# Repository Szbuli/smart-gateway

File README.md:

# Smart gateway
## build
`'docker buildx create --driver=docker-container --name=multi --use`
### mqtt-gateway
`docker buildx build -t szbuli/mqtt-gateway:latest -t szbuli/mqtt-gateway:1.0.1 --platform linux/arm64,linux/arm64/v8 --push .`
### resource-monitor
`docker buildx build -t szbuli/resource-monitor:latest -t szbuli/resource-monitor:1.0.0 --platform linux/arm64,linux/arm64/v8 --push .`
## deploy

- start and upgrade
`sudo docker compose up --detach`
- logs
`sudo docker compose logs -f -t`
- restart a single service
`sudo docker compose restart zigbee2mqtt`

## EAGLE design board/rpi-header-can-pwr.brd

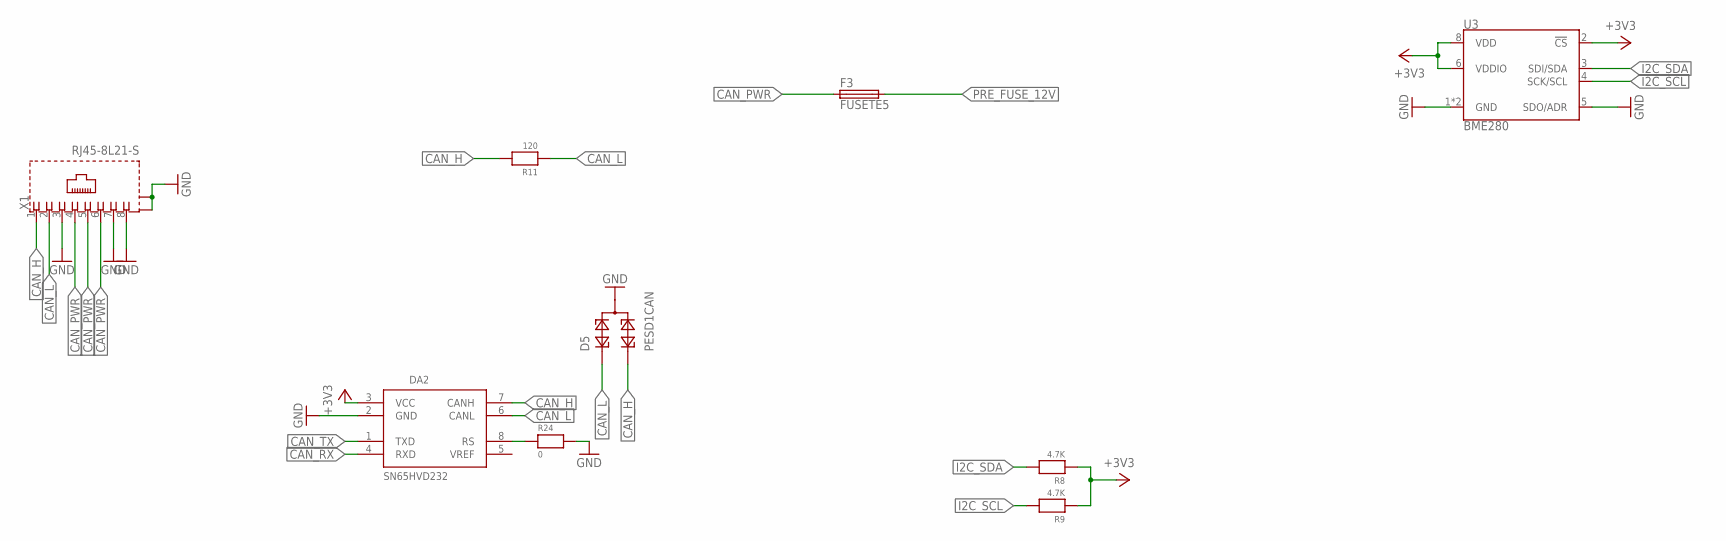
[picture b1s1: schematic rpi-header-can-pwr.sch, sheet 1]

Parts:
D5: PESD1CAN; SOT23
DA2: SN65HVD232; SO08
F3: FUSETE5; TE5
R8, R9: 4.7K; 0603
R11: 120; 0603
R24: 0; 0603
U3: BME280; LGA-8-2.5X2.5
X1: RJ45-8L21-S; RJ45-SHIELD1

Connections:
+3V3: DA2.3 (VCC), R8.1, R9.1, U3.2 (!CS), U3.6 (VDDIO), U3.8 (VDD); also elsewhere on the board
CAN_H: D5.2, DA2.7 (CANH), R11.2, X1.1
CAN_L: D5.1, DA2.6 (CANL), R11.1, X1.2
CAN_PWR: F3.1, X1.4, X1.5, X1.6
CAN_RX: DA2.4 (RXD); also elsewhere on the board
CAN_TX: DA2.1 (TXD); also elsewhere on the board
GND: D5.3, DA2.2 (GND), R24.2, U3.1 (GND), U3.5 (SDO/ADR), U3.7 (GND), X1.3, X1.7, X1.8, X1.S1 (S), X1.S2 (S); also elsewhere on the board
I2C_SCL: R9.2, U3.4 (SCK/SCL); also elsewhere on the board
I2C_SDA: R8.2, U3.3 (SDI/SDA); also elsewhere on the board
unnamed: DA2.8 (RS), R24.1
PRE_FUSE_12V: F3.2; also elsewhere on the board

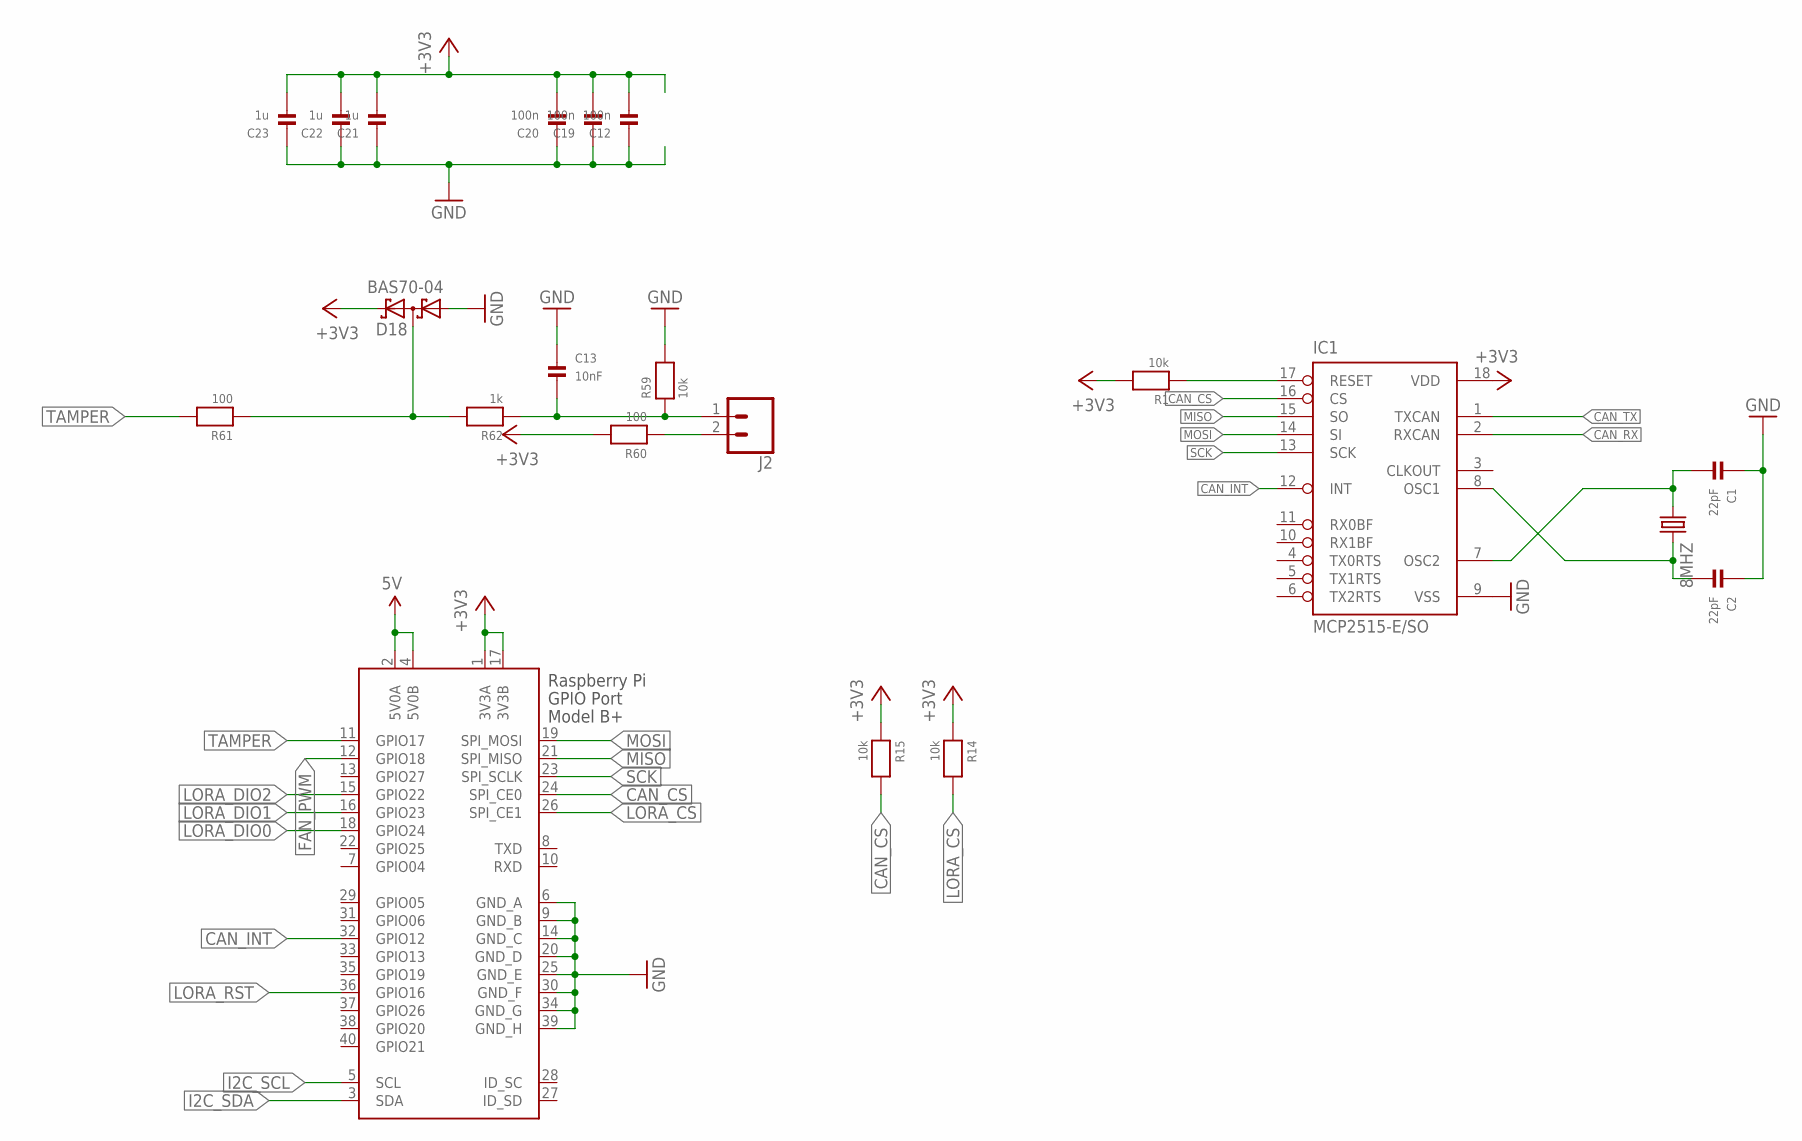
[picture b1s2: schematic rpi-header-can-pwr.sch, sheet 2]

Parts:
8MHZ: CRYSTALHC49UP; HC49UP
C1, C2: 22pF; 0603
C12, C19, C20: 100n; 0603
C13: 10nF; 0603
C21, C22, C23: 1u; 0603
D18: BAS70-04; SOT23
IC1: MCP2515-E/SO; SO18L
J2: CONN_023.5MM; SCREWTERMINAL-3.5MM-2
R1, R14, R15, R59: 10k; 0603
R60, R61: 100; 0603
R62: 1k; 0603
X2: RASPI_BOARD_B+#_E3; RASPI_BOARD_B+_EDGES_3DRILL

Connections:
5V: X2.2 (5V0A), X2.4 (5V0B); also elsewhere on the board
+3V3: C12.2, C19.2, C20.2, C21.2, C22.2, C23.2, D18.2 (C2), IC1.18 (VDD), R1.2, R14.1, R15.1, R60.2, X2.1 (3V3A), X2.17 (3V3B); also elsewhere on the board
ASDASD: D18.3 (C1A2), R61.1, R62.2
CAN_CS: IC1.16 (CS), R15.2, X2.24 (SPI_CE0)
CAN_INT: IC1.12 (INT), X2.32 (GPIO12)
CAN_RX: IC1.2 (RXCAN); also elsewhere on the board
CAN_TX: IC1.1 (TXCAN); also elsewhere on the board
FAN_PWM: X2.12 (GPIO18); also elsewhere on the board
GND: C1.1, C2.1, C12.1, C13.1, C19.1, C20.1, C21.1, C22.1, C23.1, D18.1 (A1), IC1.9 (VSS), R59.2, X2.6 (GND_A), X2.9 (GND_B), X2.14 (GND_C), X2.20 (GND_D), X2.25 (GND_E), X2.30 (GND_F), X2.34 (GND_G), X2.39 (GND_H); also elsewhere on the board
I2C_SCL: X2.5 (SCL); also elsewhere on the board
I2C_SDA: X2.3 (SDA); also elsewhere on the board
LORA_CS: R14.2, X2.26 (SPI_CE1); also elsewhere on the board
LORA_DIO0: X2.18 (GPIO24); also elsewhere on the board
LORA_DIO1: X2.16 (GPIO23); also elsewhere on the board
LORA_DIO2: X2.15 (GPIO22); also elsewhere on the board
LORA_RST: X2.36 (GPIO16); also elsewhere on the board
MISO: IC1.15 (SO), X2.21 (SPI_MISO); also elsewhere on the board
MOSI: IC1.14 (SI), X2.19 (SPI_MOSI); also elsewhere on the board
unnamed: 8MHZ.2, C2.2, IC1.8 (OSC1)
unnamed: 8MHZ.1, C1.2, IC1.7 (OSC2)
unnamed: J2.2, R60.1
unnamed: C13.2, J2.1, R59.1, R62.1
RS: IC1.17 (RESET), R1.1
SCK: IC1.13 (SCK), X2.23 (SPI_SCLK); also elsewhere on the board
TAMPER: R61.2, X2.11 (GPIO17)

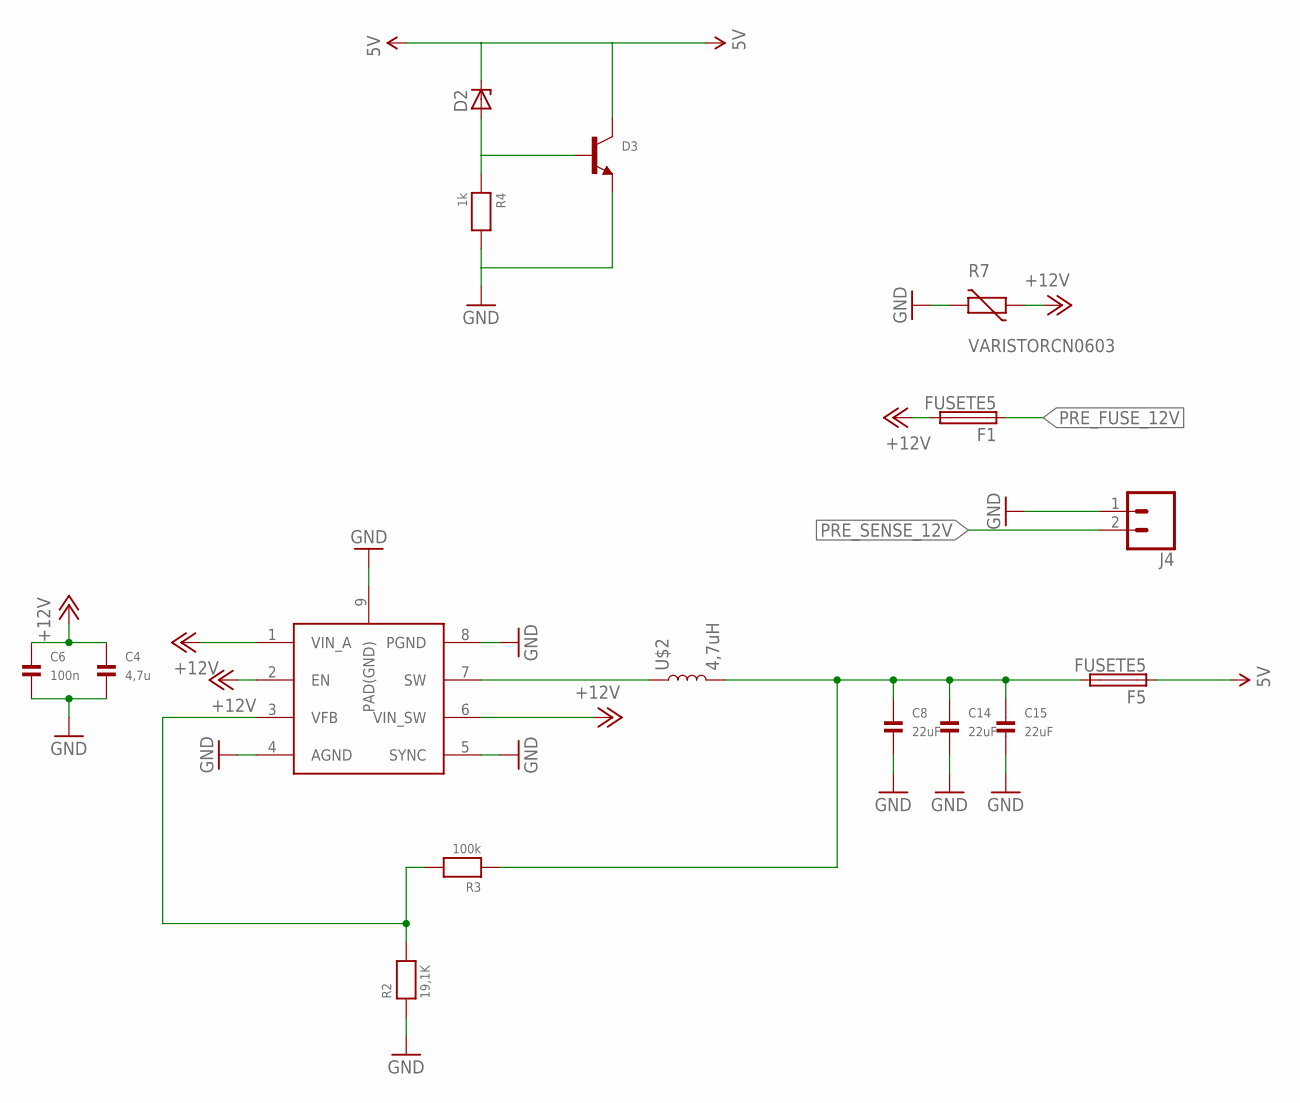
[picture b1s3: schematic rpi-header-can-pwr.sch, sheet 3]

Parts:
C4: 4,7u; 0805
C6: 100n; 0805
C8, C14, C15: 22uF; 0805
D2: ZENER-DIODESOD80C; SOD80C
D3: TRANSISTOR_NPNWIDE; SOT23-WIDE
F1, F5: FUSETE5; TE5
J4: CONN_025MM; SCREWTERMINAL-5MM-2
R2: 19,1K; 0603
R3: 100k; 0603
R4: 1k; 0603
R7: VARISTORCN0603; CT/CN0603
U$1: ST1S10; POWERSO-8
U$2: 4,7uH; 0504

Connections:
5V: D2.C, D3.3 (C), F5.1; also elsewhere on the board
+12V: C4.1, C6.1, F1.2, R7.1, U$1.1 (VIN_A), U$1.2 (EN), U$1.6 (VIN_SW)
GND: C4.2, C6.2, C8.2, C14.2, C15.2, D3.2 (E), J4.1, R2.1, R4.2, R7.2, U$1.4 (AGND), U$1.5 (SYNC), U$1.8 (PGND), U$1.9 (PAD(GND)); also elsewhere on the board
unnamed: R2.2, R3.2, U$1.3 (VFB)
unnamed: D2.A, D3.1 (B), R4.1
unnamed: U$1.7 (SW), U$2.1
unnamed: C8.1, C14.1, C15.1, F5.2, R3.1, U$2.2
PRE_FUSE_12V: F1.1; also elsewhere on the board
PRE_SENSE_12V: J4.2; also elsewhere on the board

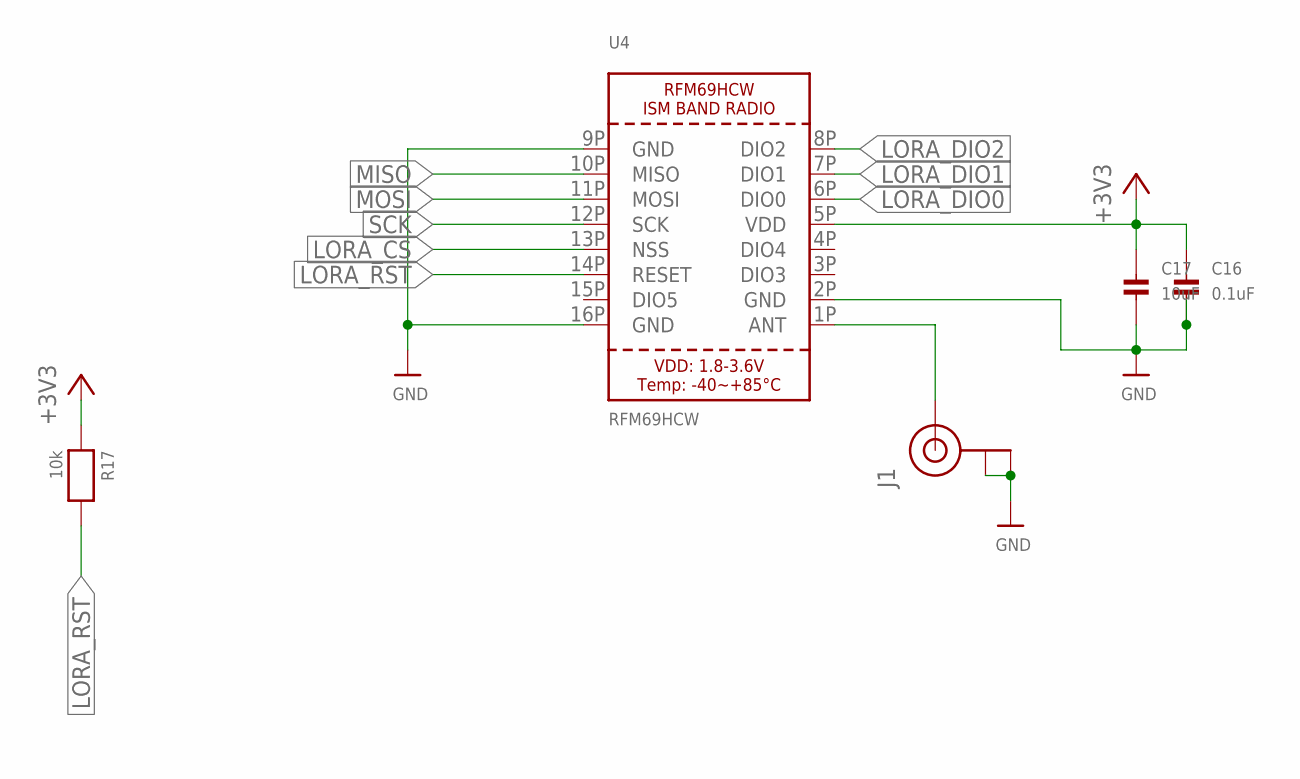
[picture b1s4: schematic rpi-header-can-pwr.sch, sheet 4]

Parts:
C16: 0.1uF; 0603
C17: 10uF; 0603
J1: U.FL
R17: 10k; 0603
U4: RFM69HCW; RFMHCW_SMT

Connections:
+3V3: C16.1, C17.1, R17.1, U4.5P (VDD); also elsewhere on the board
GND: C16.2, C17.2, J1.P$1 (GND), J1.P$2 (GND), U4.2P (GND), U4.9P (GND), U4.16P (GND); also elsewhere on the board
LORA_CS: U4.13P (NSS); also elsewhere on the board
LORA_DIO0: U4.6P (DIO0); also elsewhere on the board
LORA_DIO1: U4.7P (DIO1); also elsewhere on the board
LORA_DIO2: U4.8P (DIO2); also elsewhere on the board
LORA_RST: R17.2, U4.14P (RESET); also elsewhere on the board
MISO: U4.10P (MISO); also elsewhere on the board
MOSI: U4.11P (MOSI); also elsewhere on the board
unnamed: J1.P$3 (SIGNAL), U4.1P (ANT)
SCK: U4.12P (SCK); also elsewhere on the board

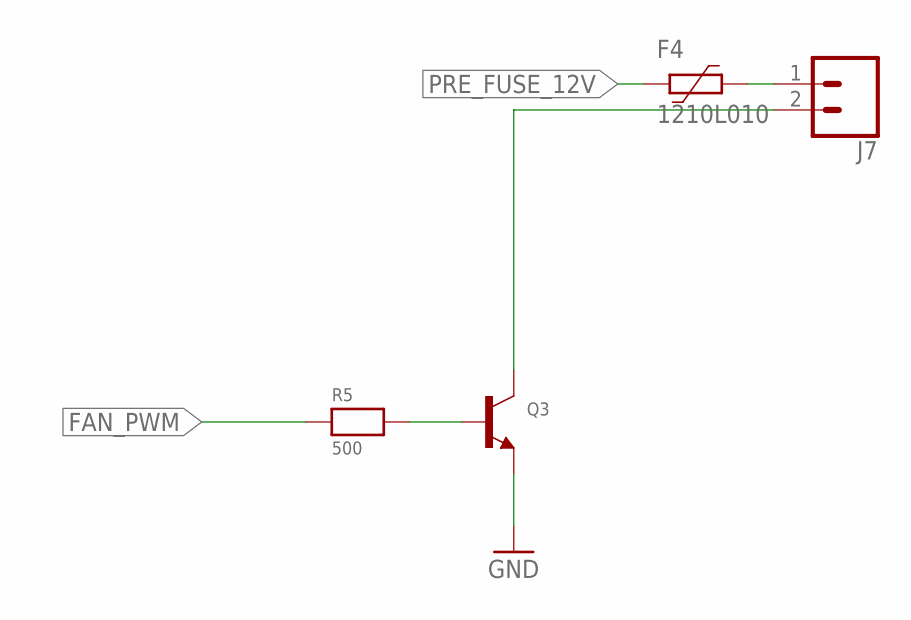
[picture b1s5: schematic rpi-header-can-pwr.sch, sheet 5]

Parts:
F4: 1210L010; 1210L
J7: CONN_023.5MM; SCREWTERMINAL-3.5MM-2
Q3: TRANSISTOR_NPNWIDE; SOT23-WIDE
R5: 500; 0603

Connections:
FAN_PWM: R5.1; also elsewhere on the board
GND: Q3.2 (E); also elsewhere on the board
unnamed: Q3.1 (B), R5.2
unnamed: F4.1, J7.1
unnamed: J7.2, Q3.3 (C)
PRE_FUSE_12V: F4.2; also elsewhere on the board

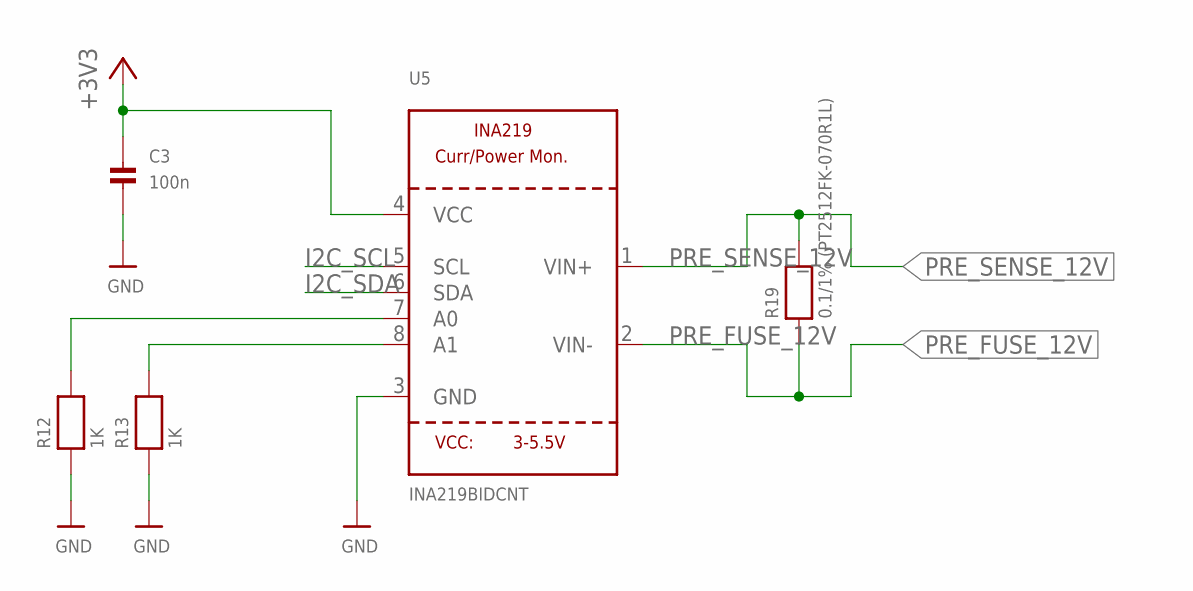
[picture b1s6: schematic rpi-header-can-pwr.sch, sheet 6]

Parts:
C3: 100n; 0603
R12, R13: 1K; 0603
R19: 0.1/1% (PT2512FK-070R1L); 2512
U5: INA219BIDCNT; SOT23-8

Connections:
+3V3: C3.1, U5.4 (VCC); also elsewhere on the board
GND: C3.2, R12.1, R13.1, U5.3 (GND); also elsewhere on the board
I2C_SCL: U5.5 (SCL); also elsewhere on the board
I2C_SDA: U5.6 (SDA); also elsewhere on the board
unnamed: R13.2, U5.8 (A1)
unnamed: R12.2, U5.7 (A0)
PRE_FUSE_12V: R19.1, U5.2 (VIN-); also elsewhere on the board
PRE_SENSE_12V: R19.2, U5.1 (VIN+); also elsewhere on the board

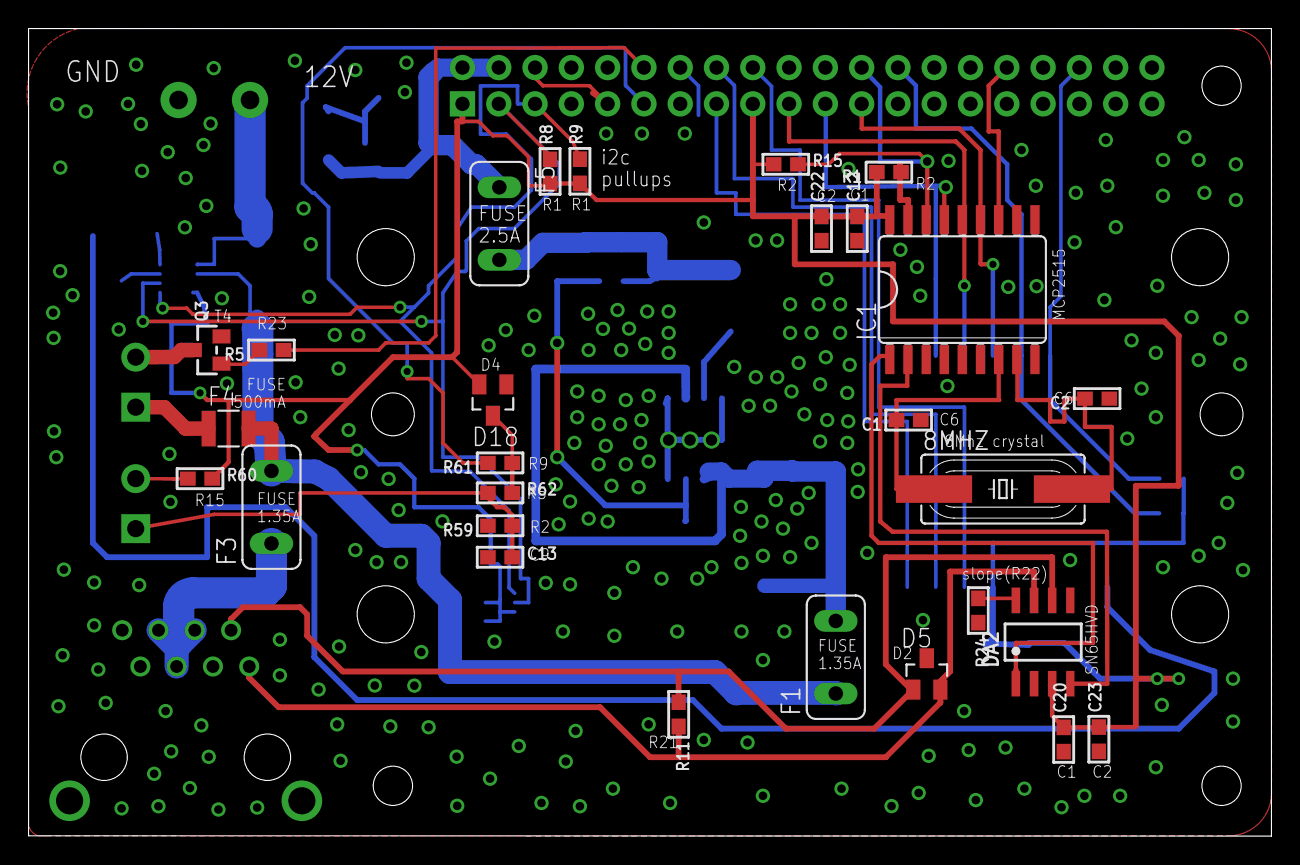
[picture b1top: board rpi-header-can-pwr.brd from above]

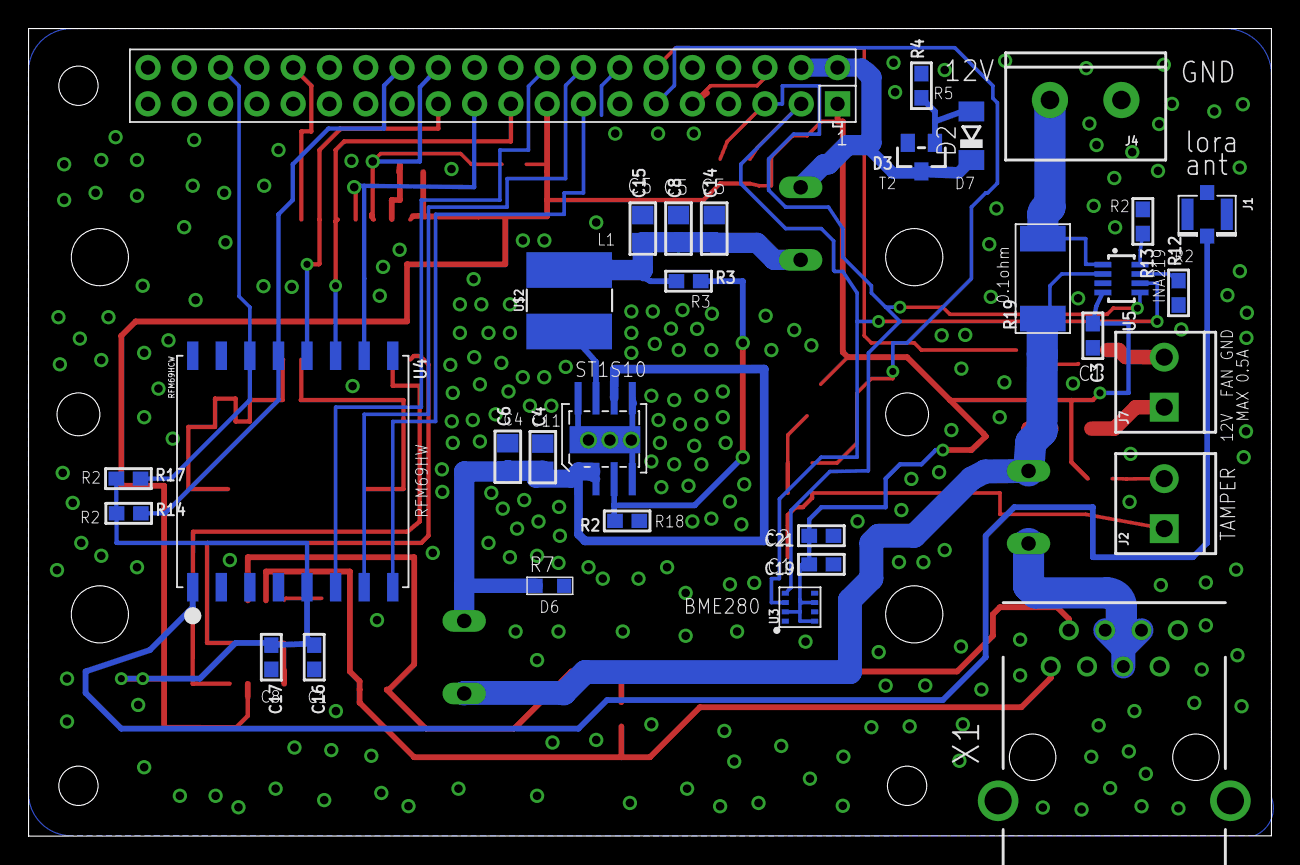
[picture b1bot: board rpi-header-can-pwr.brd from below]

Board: 2 copper layers, 87.0 x 56.5 mm, 62 parts (33 on the bottom side), 42 nets.

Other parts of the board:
U$3, U$4: C45-DIN-MOUNT-2-HOLE

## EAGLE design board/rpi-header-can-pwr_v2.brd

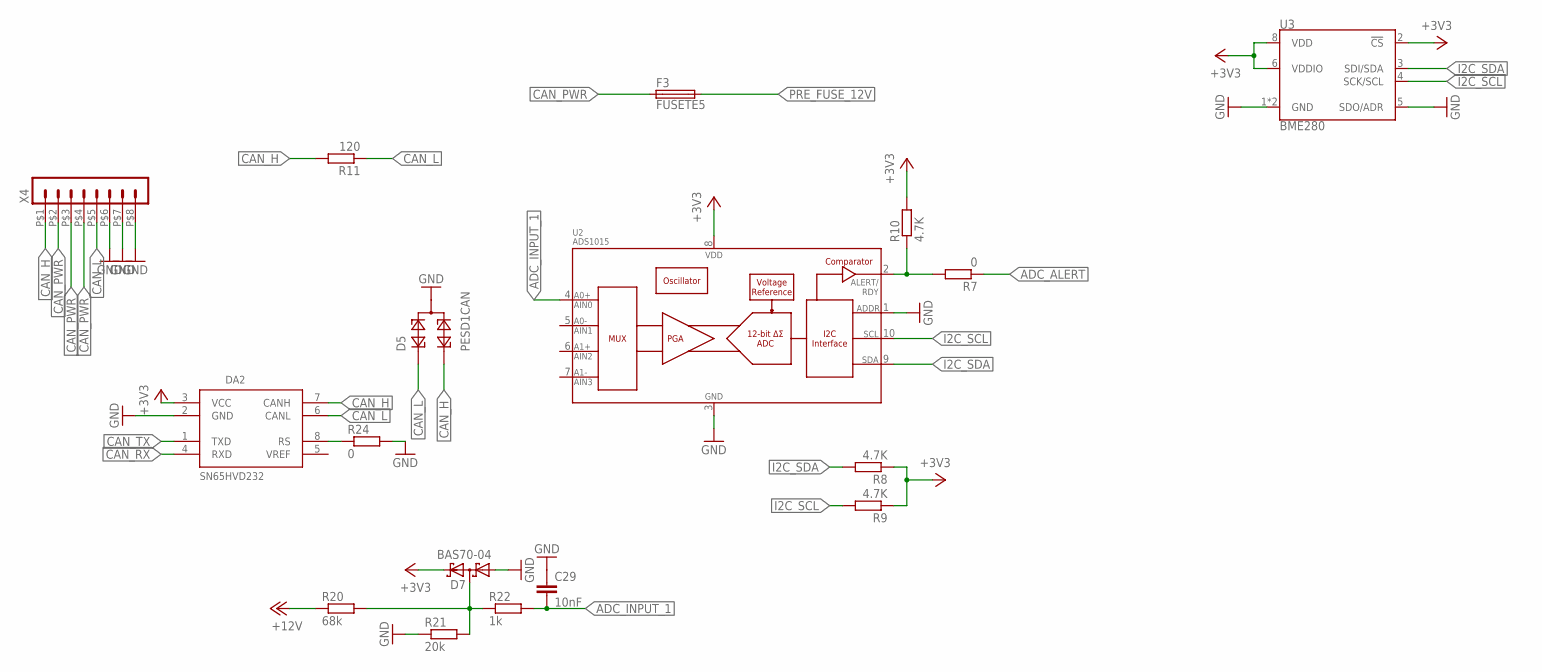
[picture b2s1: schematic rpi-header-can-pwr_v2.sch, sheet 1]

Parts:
C29: 10nF; C0603
D5: PESD1CAN; SOT23
D7: BAS70-04; SOT23
DA2: SN65HVD232; SO08
F3: FUSETE5; TE5
R7, R24: 0; R0603
R8, R9, R10: 4.7K; R0603
R11: 120; R0603
R20: 68k; R0603
R21: 20k; R0603
R22: 1k; R0603
U2: ADS1015; MSOP10
U3: BME280; LGA-8-2.5X2.5
X4: HEADER_POS8_43045-0812; 43045-0812

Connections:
12V_REFERENCE4: D7.3 (C1A2), R20.2, R21.2, R22.1
+3V3: D7.2 (C2), DA2.3 (VCC), R8.1, R9.1, R10.2, U2.8 (VDD), U3.2 (!CS), U3.6 (VDDIO), U3.8 (VDD); also elsewhere on the board
+12V: R20.1; also elsewhere on the board
ADC_ALERT: R7.1; also elsewhere on the board
ADC_INPUT_1: C29.2, R22.2, U2.4 (AIN0)
CAN_H: D5.2, DA2.7 (CANH), R11.2, X4.P$1 (1)
CAN_L: D5.1, DA2.6 (CANL), R11.1, X4.P$5 (5)
CAN_PWR: F3.1, X4.P$2 (2), X4.P$3 (3), X4.P$4 (4)
CAN_RX: DA2.4 (RXD); also elsewhere on the board
CAN_TX: DA2.1 (TXD); also elsewhere on the board
GND: C29.1, D5.3, D7.1 (A1), DA2.2 (GND), R21.1, R24.2, U2.1 (ADDR), U2.3 (VSS), U3.1 (GND), U3.5 (SDO/ADR), U3.7 (GND), X4.P$6 (6), X4.P$7 (7), X4.P$8 (8); also elsewhere on the board
I2C_SCL: R9.2, U2.10 (SCL), U3.4 (SCK/SCL); also elsewhere on the board
I2C_SDA: R8.2, U2.9 (SDA), U3.3 (SDI/SDA); also elsewhere on the board
unnamed: R7.2, R10.1, U2.2 (ALERT/RDY)
unnamed: DA2.8 (RS), R24.1
PRE_FUSE_12V: F3.2; also elsewhere on the board

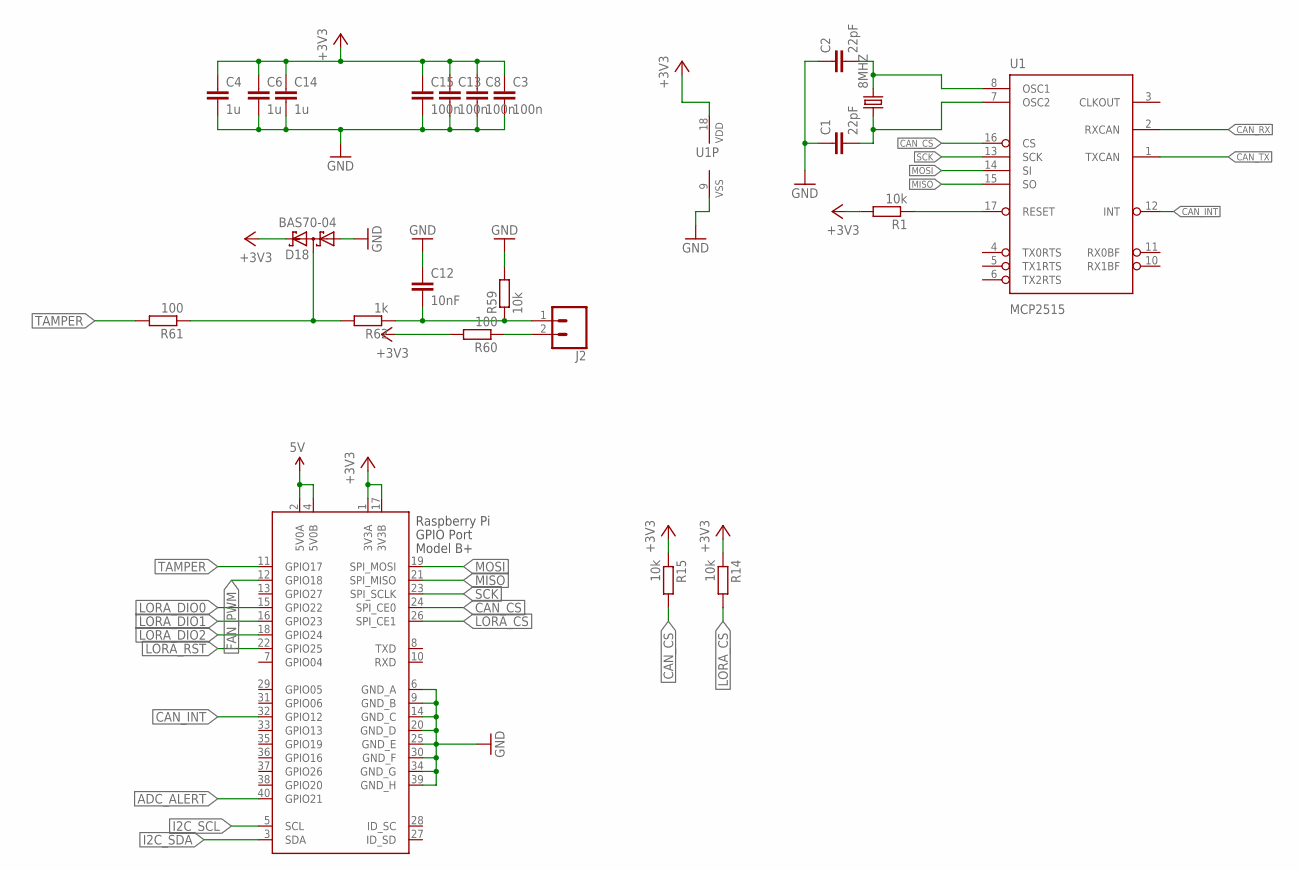
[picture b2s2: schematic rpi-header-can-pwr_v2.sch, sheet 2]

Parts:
8MHZ: CRYSTALHC49UP; HC49UP
C1, C2: 22pF; 0603-CAP
C3, C8, C13, C15: 100n; C0603
C4, C6, C14: 1u; C0603
C12: 10nF; C0603
D18: BAS70-04; SOT23
J2: CONN_023.5MM; SCREWTERMINAL-3.5MM-2
R1, R14, R15, R59: 10k; R0603
R60, R61: 100; R0603
R62: 1k; R0603
U1: MCP2515; SO-18W
X2: RASPI_BOARD_B+#_E3; RASPI_BOARD_B+_EDGES_3DRILL

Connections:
5V: X2.2 (5V0A), X2.4 (5V0B); also elsewhere on the board
+3V3: C3.1, C4.1, C6.1, C8.1, C13.1, C14.1, C15.1, D18.2 (C2), R1.2, R14.1, R15.1, R60.2, U1.18 (VDD), X2.1 (3V3A), X2.17 (3V3B); also elsewhere on the board
ADC_ALERT: X2.40 (GPIO21); also elsewhere on the board
ASDASD: D18.3 (C1A2), R61.1, R62.2
CAN_CS: R15.2, U1.16 (CS), X2.24 (SPI_CE0)
CAN_INT: U1.12 (INT), X2.32 (GPIO12)
CAN_RX: U1.2 (RXCAN); also elsewhere on the board
CAN_TX: U1.1 (TXCAN); also elsewhere on the board
FAN_PWM: X2.12 (GPIO18); also elsewhere on the board
GND: C1.1, C2.1, C3.2, C4.2, C6.2, C8.2, C12.1, C13.2, C14.2, C15.2, D18.1 (A1), R59.2, U1.9 (VSS), X2.6 (GND_A), X2.9 (GND_B), X2.14 (GND_C), X2.20 (GND_D), X2.25 (GND_E), X2.30 (GND_F), X2.34 (GND_G), X2.39 (GND_H); also elsewhere on the board
I2C_SCL: X2.5 (SCL); also elsewhere on the board
I2C_SDA: X2.3 (SDA); also elsewhere on the board
LORA_CS: R14.2, X2.26 (SPI_CE1); also elsewhere on the board
LORA_DIO0: X2.15 (GPIO22); also elsewhere on the board
LORA_DIO1: X2.16 (GPIO23); also elsewhere on the board
LORA_DIO2: X2.18 (GPIO24); also elsewhere on the board
LORA_RST: X2.22 (GPIO25); also elsewhere on the board
MISO: U1.15 (SO), X2.21 (SPI_MISO); also elsewhere on the board
MOSI: U1.14 (SI), X2.19 (SPI_MOSI); also elsewhere on the board
unnamed: 8MHZ.2, C2.2, U1.8 (OSC1)
unnamed: 8MHZ.1, C1.2, U1.7 (OSC2)
unnamed: J2.2, R60.1
unnamed: C12.2, J2.1, R59.1, R62.1
RS: R1.1, U1.17 (RESET)
SCK: U1.13 (SCK), X2.23 (SPI_SCLK); also elsewhere on the board
TAMPER: R61.2, X2.11 (GPIO17)

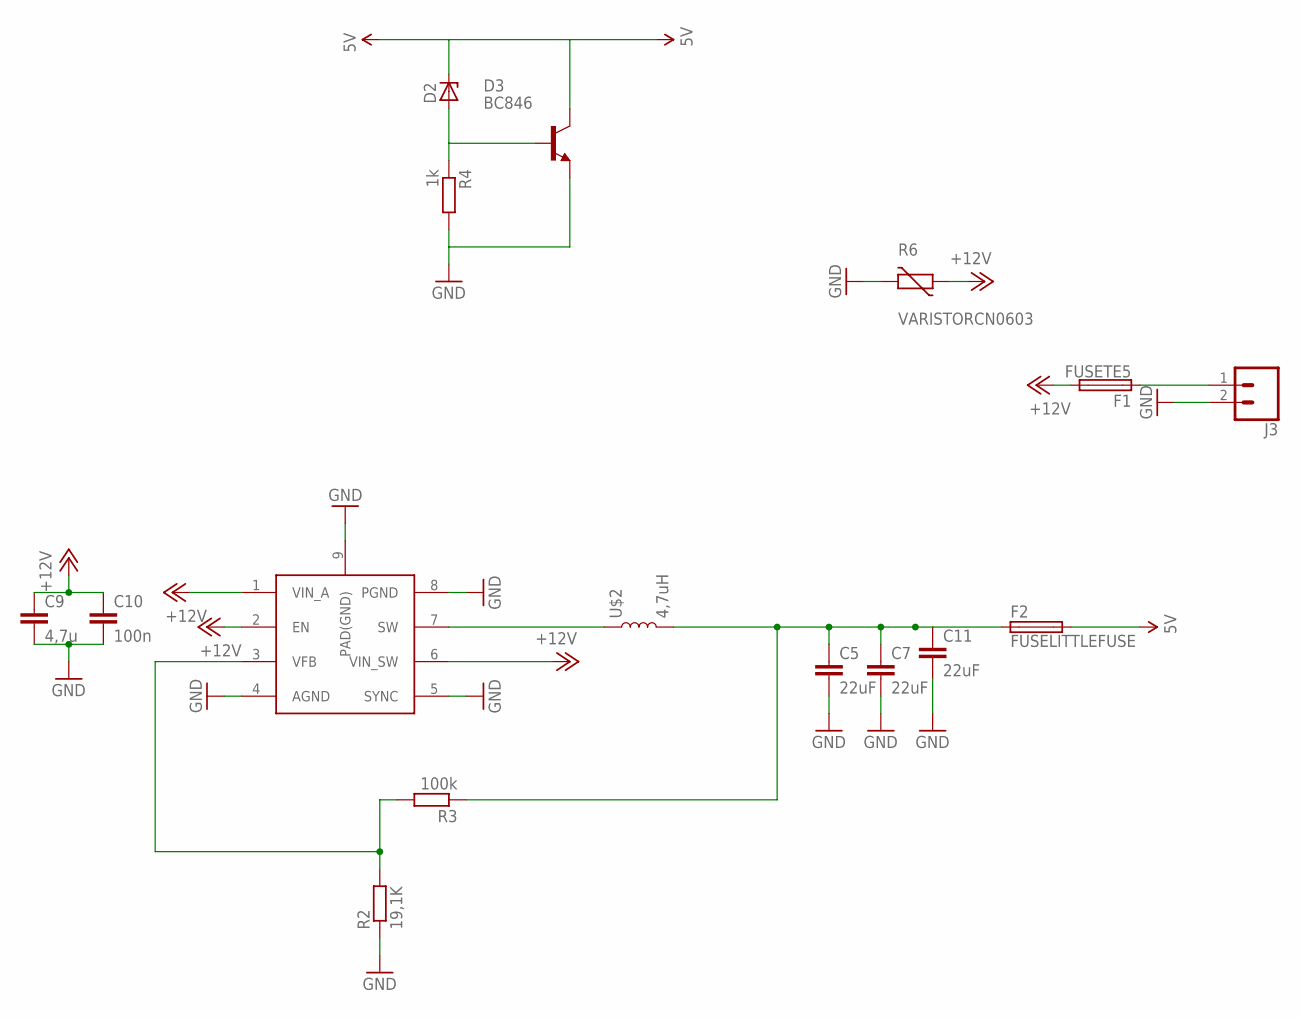
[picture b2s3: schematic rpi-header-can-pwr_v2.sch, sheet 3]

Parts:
C5, C7, C11: 22uF; C1206
C9: 4,7u; C0805
C10: 100n; C0805
D2: ZENER-DIODESOD80C; SOD80C
D3: BC846; SOT23
F1: FUSETE5; TE5
F2: FUSELITTLEFUSE; LITTLEFUSE
J3: CONN_025MM; SCREWTERMINAL-5MM-2
R2: 19,1K; R0603
R3: 100k; R0603
R4: 1k; R0603
R6: VARISTORCN0603; CT/CN0603
U$1: ST1S10; POWERSO-8
U$2: 4,7uH; 0504

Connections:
5V: D2.C, D3.3 (C), F2.2; also elsewhere on the board
+12V: C9.1, C10.1, F1.2, R6.1, U$1.1 (VIN_A), U$1.2 (EN), U$1.6 (VIN_SW); also elsewhere on the board
GND: C5.2, C7.2, C9.2, C10.2, C11.2, D3.2 (E), J3.2, R2.1, R4.2, R6.2, U$1.4 (AGND), U$1.5 (SYNC), U$1.8 (PGND), U$1.9 (PAD(GND)); also elsewhere on the board
unnamed: R2.2, R3.2, U$1.3 (VFB)
unnamed: D2.A, D3.1 (B), R4.1
unnamed: U$1.7 (SW), U$2.1
unnamed: C5.1, C7.1, C11.1, F2.1, R3.1, U$2.2
PRE_FUSE_12V: F1.1, J3.1; also elsewhere on the board

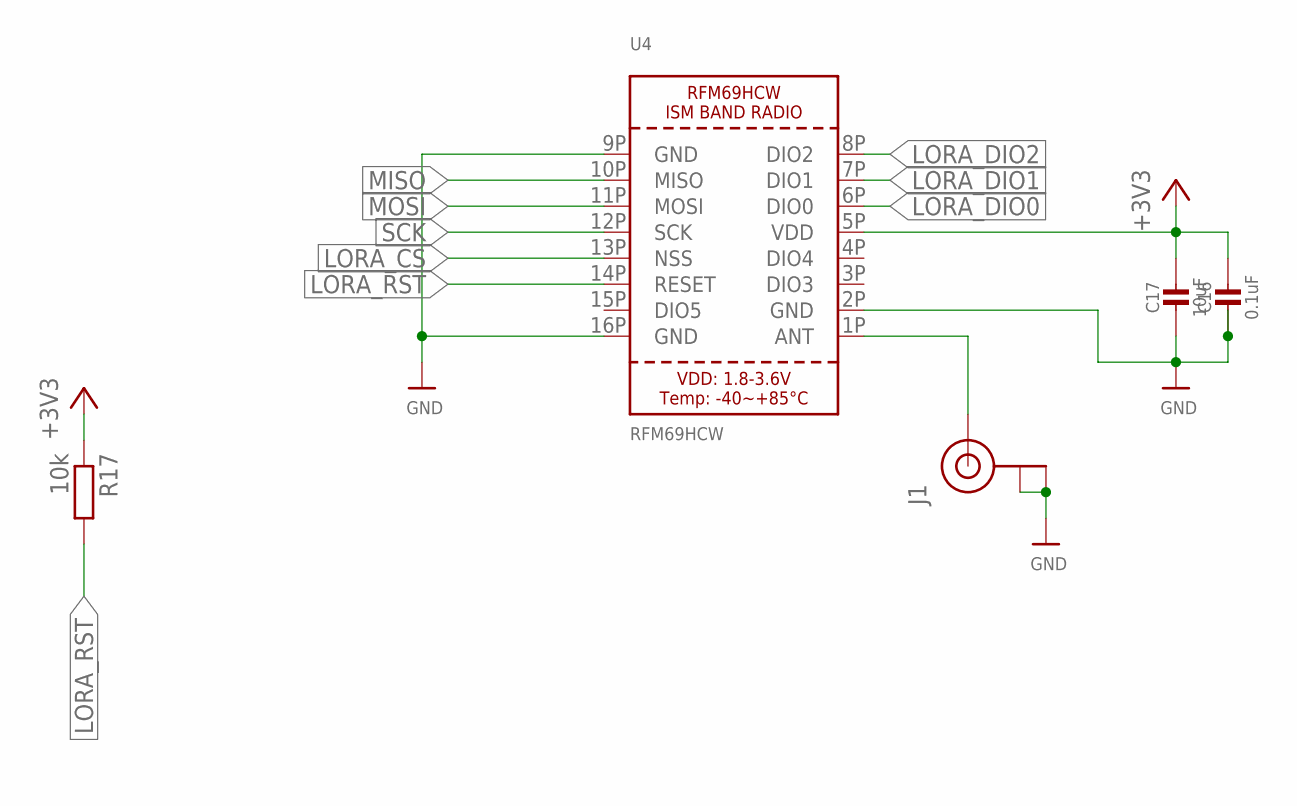
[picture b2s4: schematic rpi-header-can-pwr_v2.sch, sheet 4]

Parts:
C16: 0.1uF; 0603-NO
C17: 10uF; 0805-NO
J1: U.FL
R17: 10k; R0603
U4: RFM69HCW; RFMHCW_SMT

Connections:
+3V3: C16.1, C17.1, R17.1, U4.5P (VDD); also elsewhere on the board
GND: C16.2, C17.2, J1.P$1 (GND), J1.P$2 (GND), U4.2P (GND), U4.9P (GND), U4.16P (GND); also elsewhere on the board
LORA_CS: U4.13P (NSS); also elsewhere on the board
LORA_DIO0: U4.6P (DIO0); also elsewhere on the board
LORA_DIO1: U4.7P (DIO1); also elsewhere on the board
LORA_DIO2: U4.8P (DIO2); also elsewhere on the board
LORA_RST: R17.2, U4.14P (RESET); also elsewhere on the board
MISO: U4.10P (MISO); also elsewhere on the board
MOSI: U4.11P (MOSI); also elsewhere on the board
unnamed: J1.P$3 (SIGNAL), U4.1P (ANT)
SCK: U4.12P (SCK); also elsewhere on the board

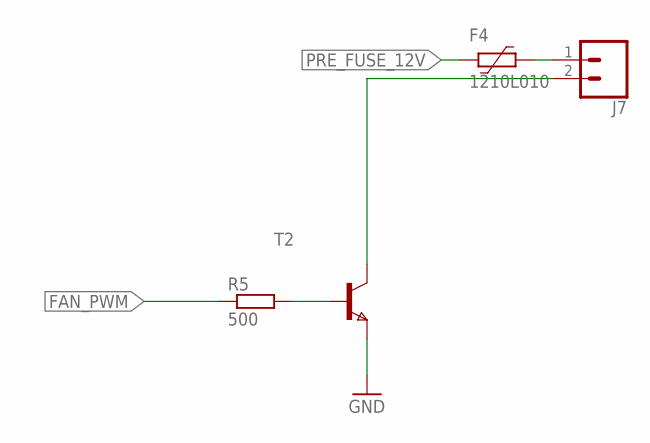
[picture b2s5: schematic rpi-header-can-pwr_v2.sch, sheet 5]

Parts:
F4: 1210L010; 1210L
J7: CONN_023.5MM; SCREWTERMINAL-3.5MM-2
R5: 500; R0603
T2: NPNSOT23; SOT-23

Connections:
FAN_PWM: R5.1; also elsewhere on the board
GND: T2.2 (E); also elsewhere on the board
unnamed: R5.2, T2.3 (B)
unnamed: F4.1, J7.1
unnamed: J7.2, T2.1 (C)
PRE_FUSE_12V: F4.2; also elsewhere on the board

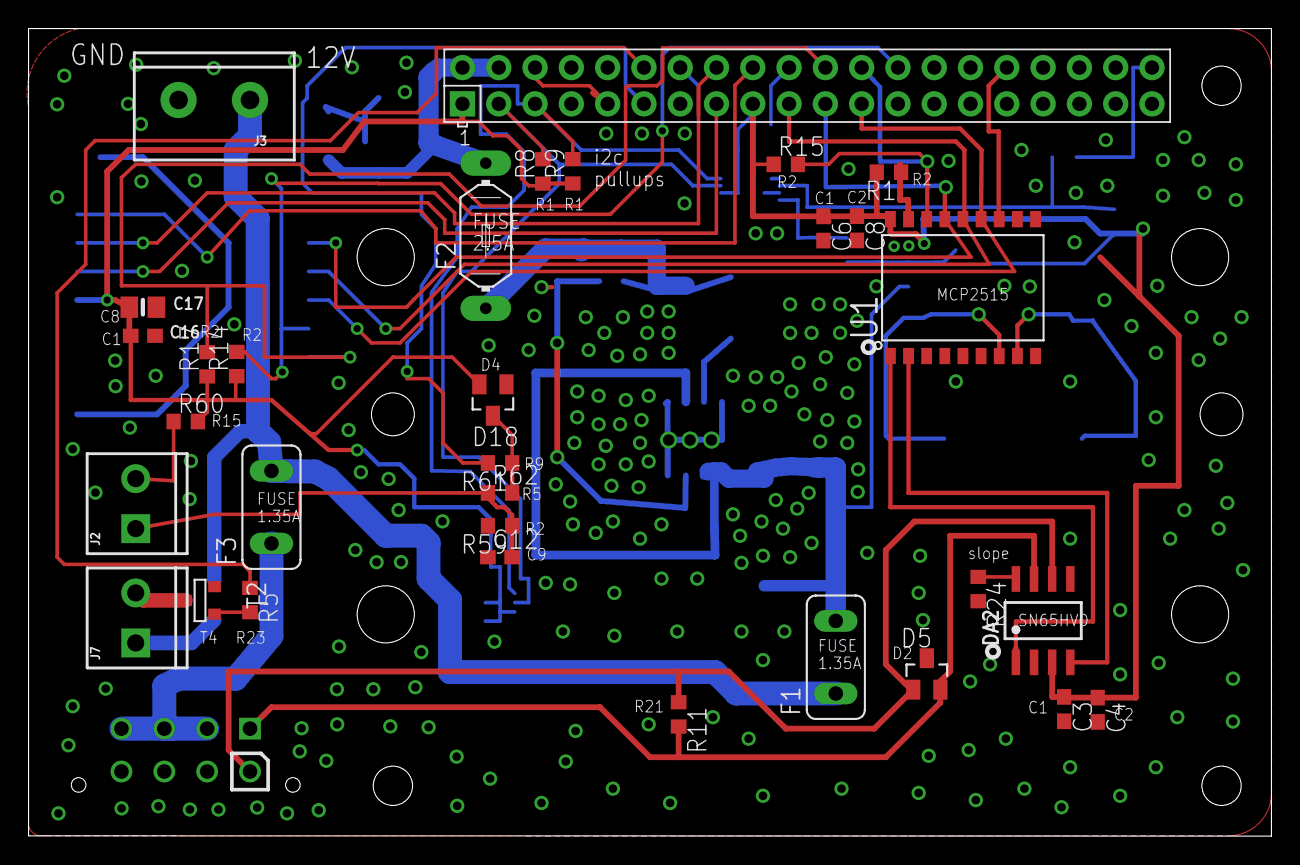
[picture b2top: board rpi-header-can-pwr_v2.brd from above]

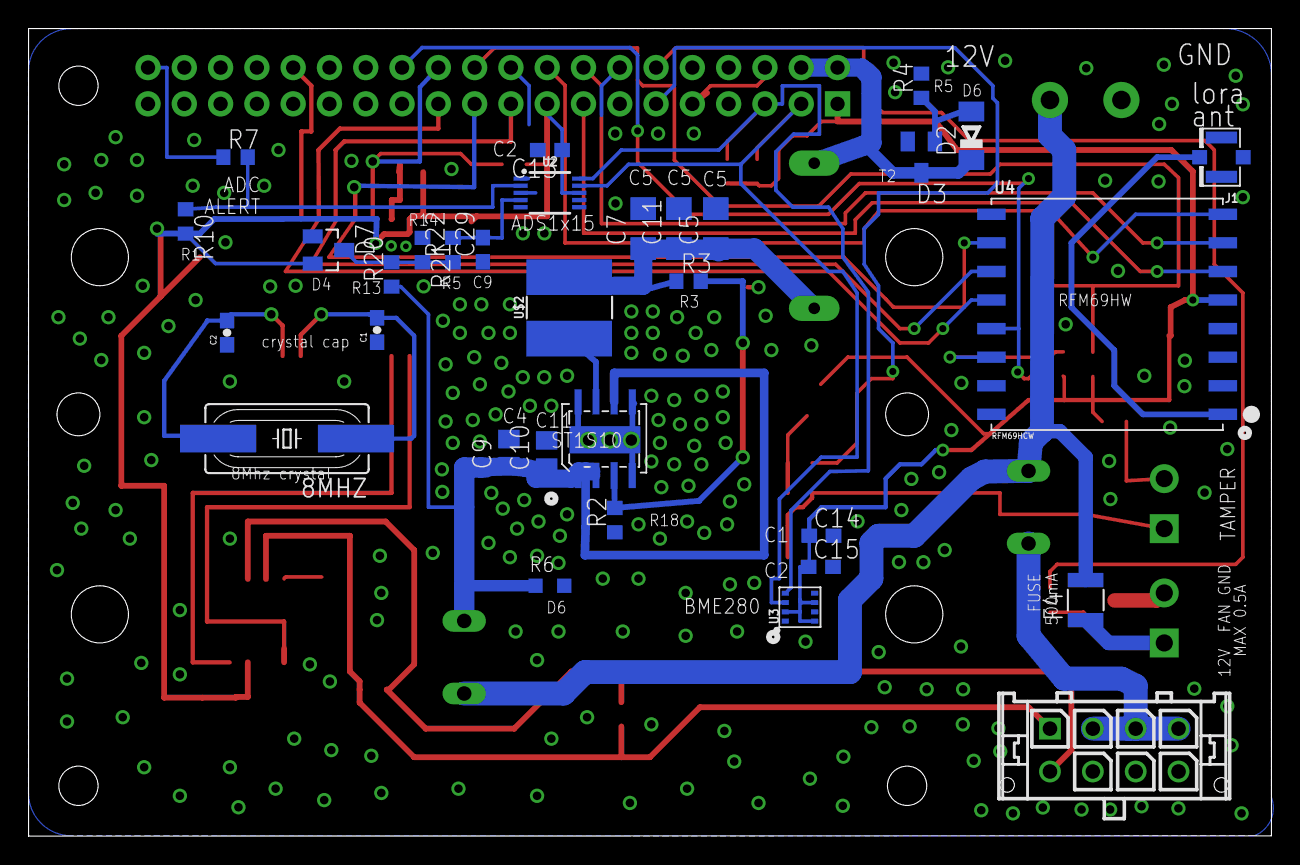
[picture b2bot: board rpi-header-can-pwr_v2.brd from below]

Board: 2 copper layers, 87.0 x 56.5 mm, 66 parts (34 on the bottom side), 43 nets.

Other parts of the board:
U$3, U$4: C45-DIN-MOUNT-2-HOLE

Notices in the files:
parts and their libraries:
SparkFun-Sensors: Licensing: Creative Commons ShareAlike 4.0 International - https://creativecommons.org/licenses/by-sa/4.0
microbuilder: This work is placed in the public domain, and may be freely used for commercial and non-commercial work with the following conditions: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
